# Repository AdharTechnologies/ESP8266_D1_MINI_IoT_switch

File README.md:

# ESP8266_D1_MINI_IoT_switch

# Description
This is a ESP8266 D1 Mini based IoT Switch using Blynk IoT Platform.
PCB files and code is given. Slight change in the code is needed and you are good to go.

kindly read this blog for full understanding: https://docs.google.com/document/d/e/2PACX-1vSAi6zmGvRynDwE_vqRe5kNtlbvM_ZqgKHYD9E6emAaTxG17WCH_XLFxFSK3p-E7R5uc0UGJ3i0j8vB/pub

# Embedded CTG

Facebook:https://www.facebook.com/profile.php?id=61558436573900

Youtube: https://www.youtube.com/@EmbeddedCTG

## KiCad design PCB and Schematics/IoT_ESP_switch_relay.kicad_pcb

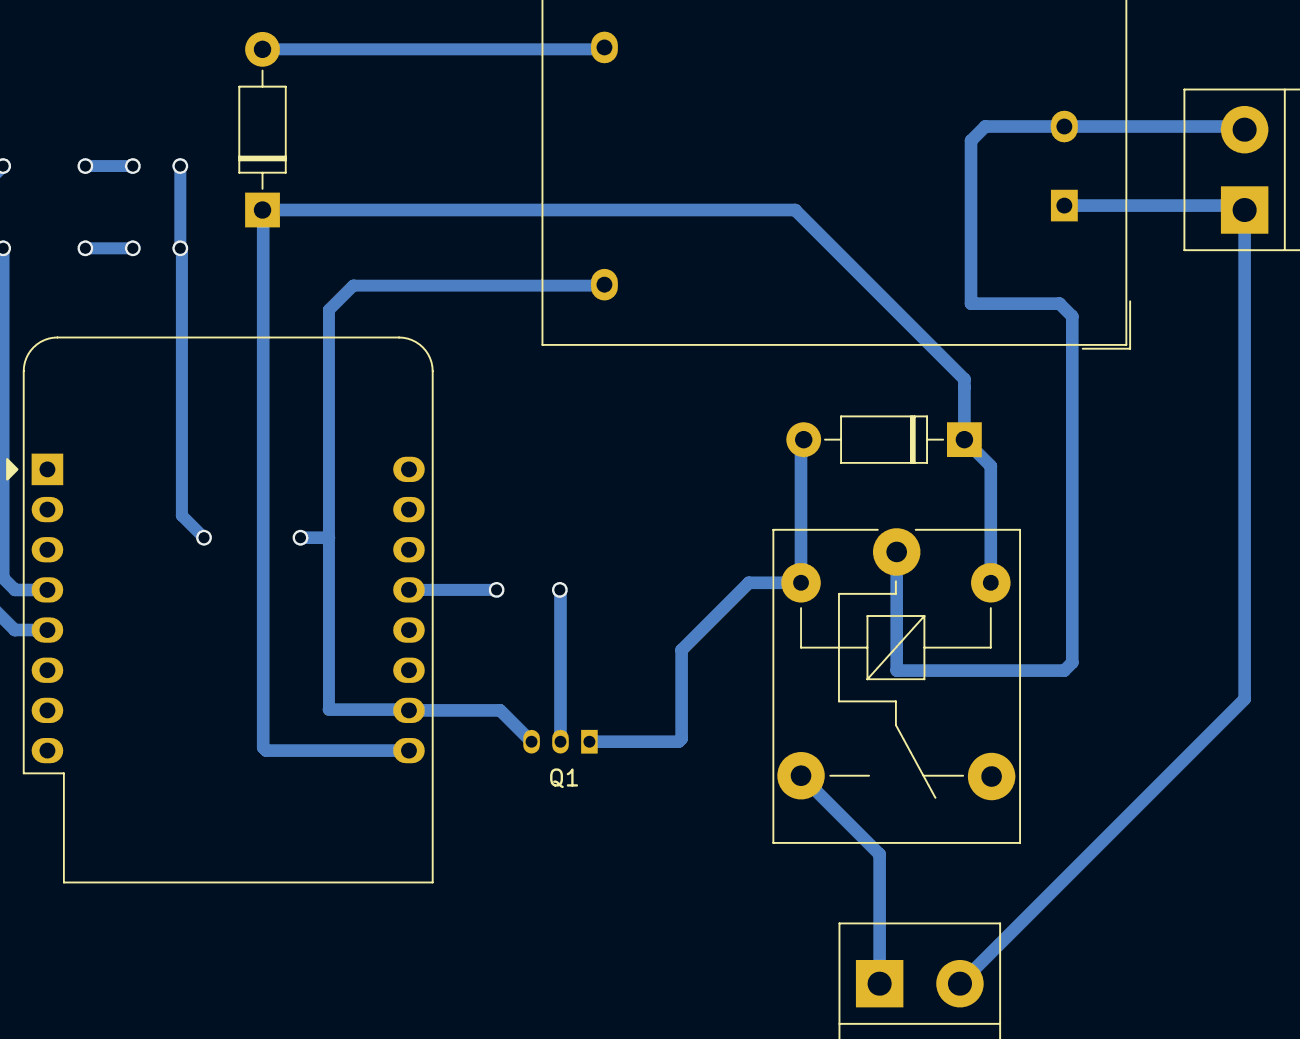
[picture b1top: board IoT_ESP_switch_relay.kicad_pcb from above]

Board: 2 copper layers, 6 parts (0 on the bottom side), 4 nets.

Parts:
D1, D4: 1N4001; D_DO-41_SOD81_P10.16mm_Horizontal
K2: SANYOU_SRD_Form_C; Relay_SPDT_SANYOU_SRD_Series_Form_C
PS1: HLK-PM01; Converter_ACDC_Hi-Link_HLK-PMxx
Q1: BC547; TO-92_Inline
U1: WeMos_D1_mini; WEMOS_D1_mini_light

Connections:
unnamed: D1.2 (A), PS1.4 (+Vout)
unnamed: D1.1 (K), D4.1 (K), K2.5, U1.9 (5V)
unnamed: PS1.3 (-Vout), Q1.3 (E), U1.10 (GND)
unnamed: D4.2 (A), K2.2, Q1.1 (C)

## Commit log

2024-06-21 README.md
